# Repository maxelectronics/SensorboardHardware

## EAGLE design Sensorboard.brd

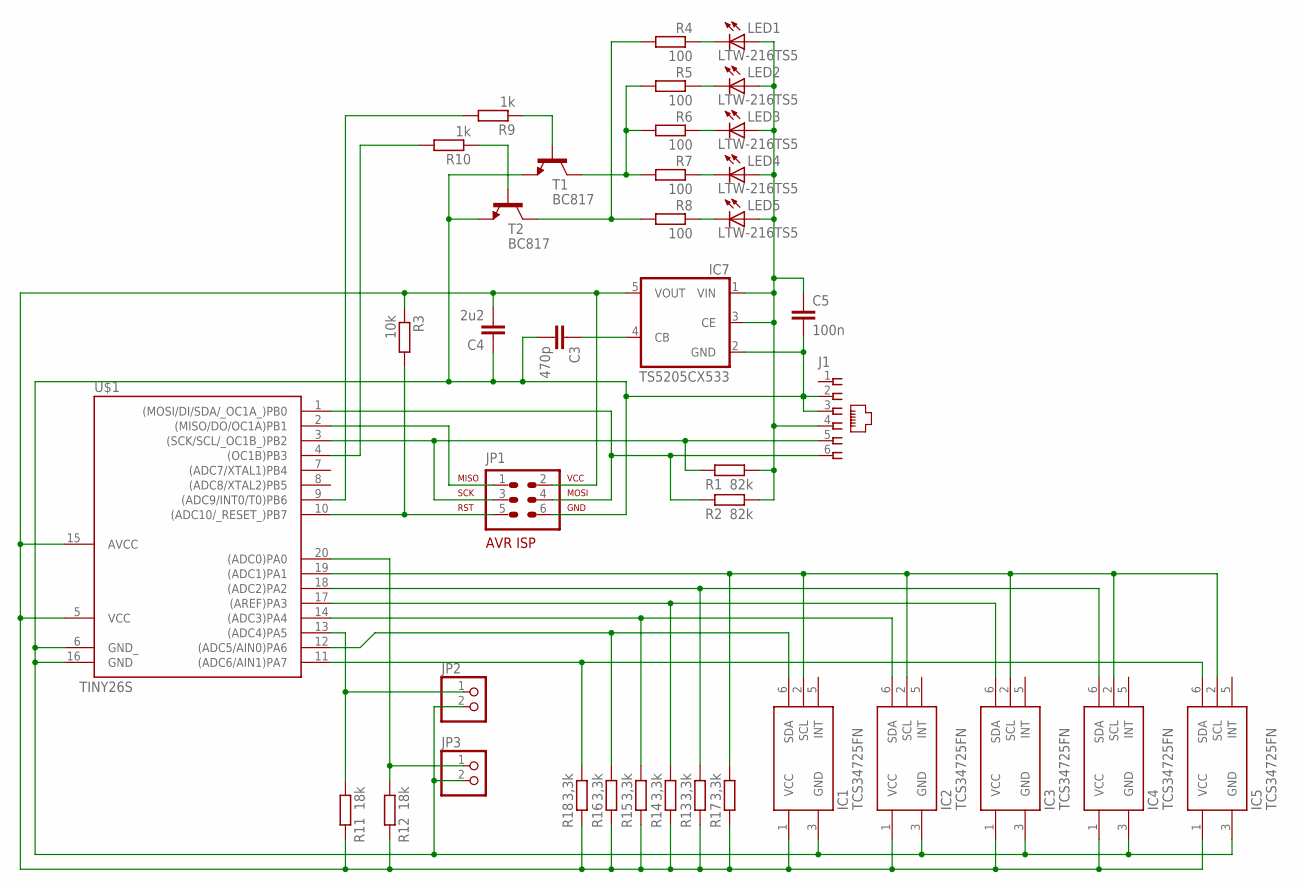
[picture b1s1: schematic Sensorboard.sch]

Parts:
C3: 470p; C2012
C4: 2u2; C2012
C5: 100n; C2012
IC1, IC2, IC3, IC4, IC5: TCS34725FN; DFN-6
IC7: TS5205CX533; SOT25
J1: NXT
JP1: AVR-ISP-6VERT; AVR-ISP-6
JP2, JP3: PINHD-1X2; 1X02
LED1, LED2, LED3, LED4, LED5: LTW-216TS5; CHIPLED_1206
R1, R2: 82k; M0805
R3: 10k; M0805
R4, R5, R6, R7, R8: 100; M0805
R9, R10: 1k; M0805
R11, R12: 18k; M0805
R13, R14, R15, R16, R17, R18: 3,3k; M0805
T1, T2: BC817; SOT23
U$1: TINY26S; SO20L$

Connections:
3,3V: C4.2, IC1.1 (VCC), IC2.1 (VCC), IC3.1 (VCC), IC4.1 (VCC), IC5.1 (VCC), IC7.5 (VOUT), JP1.2, R3.1, R11.2, R12.2, R13.2, R14.2, R15.2, R16.2, R17.2, R18.2, U$1.5 (VCC), U$1.15 (AVCC)
4,3V: C5.1, IC7.1 (VIN), IC7.3 (CE), J1.4, LED1.A, LED2.A, LED3.A, LED4.A, LED5.A, R1.1, R2.1
GND: C3.2, C4.1, C5.2, IC1.3 (GND), IC2.3 (GND), IC3.3 (GND), IC4.3 (GND), IC5.3 (GND), IC7.2 (GND), J1.2, J1.3, JP1.6, JP2.2, JP3.2, T1.2 (E), T2.2 (E), U$1.6 (GND_), U$1.16 (GND)
MISO: JP1.1, U$1.2 ((MISO/DO/OC1A)PB1)
unnamed: LED1.C, R4.1
unnamed: LED2.C, R5.1
unnamed: LED3.C, R6.1
unnamed: LED4.C, R7.1
unnamed: LED5.C, R8.1
unnamed: R5.2, R6.2, R7.2, T1.3 (C)
unnamed: C3.1, IC7.4 (CB)
unnamed: R9.2, U$1.9 ((ADC9/INT0/T0)PB6)
unnamed: R9.1, T1.1 (B)
unnamed: R4.2, R8.2, T2.3 (C)
unnamed: R10.1, T2.1 (B)
unnamed: R10.2, U$1.4 ((OC1B)PB3)
unnamed: JP2.1, R11.1, U$1.13 ((ADC4)PA5)
unnamed: JP3.1, R12.1, U$1.20 ((ADC0)PA0)
RESET: JP1.5, R3.2, U$1.10 ((ADC10/_RESET_)PB7)
SCL: IC1.2 (SCL), IC2.2 (SCL), IC3.2 (SCL), IC4.2 (SCL), IC5.2 (SCL), R17.1, U$1.19 ((ADC1)PA1)
SCL/SCK: J1.5, JP1.3, R1.2, U$1.3 ((SCK/SCL/_OC1B_)PB2)
SDA1: IC1.6 (SDA), R16.1, U$1.12 ((ADC5/AIN0)PA6)
SDA2: IC2.6 (SDA), R15.1, U$1.14 ((ADC3)PA4)
SDA3: IC3.6 (SDA), R14.1, U$1.17 ((AREF)PA3)
SDA4: IC4.6 (SDA), R13.1, U$1.18 ((ADC2)PA2)
SDA5: IC5.6 (SDA), R18.1, U$1.11 ((ADC6/AIN1)PA7)
SDA/MOSI: J1.6, JP1.4, R2.2, U$1.1 ((MOSI/DI/SDA/_OC1A_)PB0)

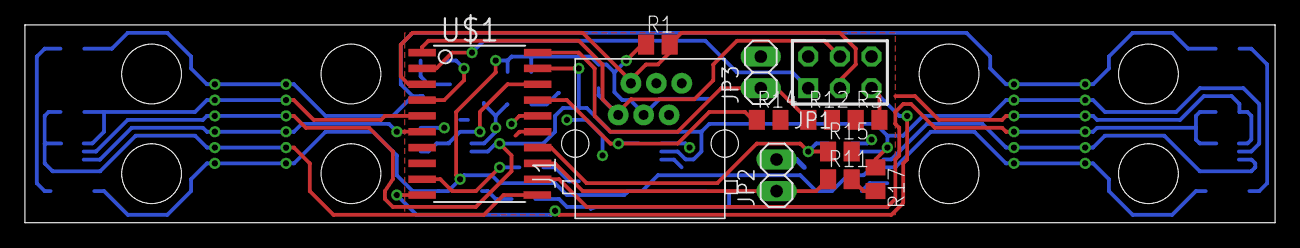
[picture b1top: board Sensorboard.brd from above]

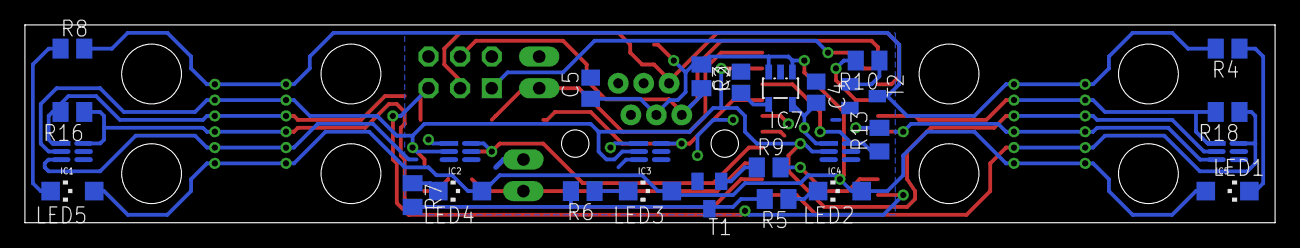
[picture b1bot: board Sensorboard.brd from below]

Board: 2 copper layers, 100.3 x 15.9 mm, 39 parts (27 on the bottom side), 27 nets.

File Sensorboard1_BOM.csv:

"Qty";"Value";"Device";"Package";"Parts";"Description";"";
"1";"";"NXT";"NXT";"J1";"6 Pin RJ-12 Connector for Lego Mindstorms NXT";"";
"2";"";"PINHD-1X2";"1X02";"JP2, JP3";"PIN HEADER";"";
"5";"100";"R-EU_M0805";"M0805";"R4, R5, R6, R7, R8";"RESISTOR, European symbol";"";
"2";"100n";"C-EUC2012";"C2012";"C4, C5";"CAPACITOR, European symbol";"";
"1";"10k";"R-EU_M0805";"M0805";"R3";"RESISTOR, European symbol";"";
"2";"18k";"R-EU_M0805";"M0805";"R11, R12";"RESISTOR, European symbol";"";
"2";"1k";"R-EU_M0805";"M0805";"R9, R10";"RESISTOR, European symbol";"";
"6";"3,3k";"R-EU_M0805";"M0805";"R13, R14, R15, R16, R17, R18";"RESISTOR, European symbol";"";
"1";"470p";"C-EUC2012";"C2012";"C3";"CAPACITOR, European symbol";"";
"2";"82k";"R-EU_M0805";"M0805";"R1, R2";"RESISTOR, European symbol";"";
"1";"AVR-ISP-6VERT";"AVR-ISP-6VERT";"AVR-ISP-6";"JP1";"AVR ISP-6 Serial Programming Header";"";
"2";"BC817";"BC846";"SOT23";"T1, T2";"NPN TRANSISTOR";"";
"5";"LTW-216TS5";"LEDCHIPLED_1206";"CHIPLED_1206";"LED1, LED2, LED3, LED4, LED5";"LED";"";
"5";"TCS34725FN";"TCS3472FN";"DFN-6";"IC1, IC2, IC3, IC4, IC5";"The TAOS inc. TCS3472 device provides a digital return of red, green, blue (RGB), and clear light sensing values. An IR";"";
"1";"TINY26S";"TINY26S";"SO20L$";"U$1";"Atmel Tiny26/261/461/861";"";
"1";"TS520533";"TS520533";"SOT25";"IC7";"150mA Low Noise LDO Voltage Regulator with Enable";"";

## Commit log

2018-11-16 Minor corrections

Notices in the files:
parts and their libraries:
HyperTriangle: Copyright HyperTriangle 2010-2011
